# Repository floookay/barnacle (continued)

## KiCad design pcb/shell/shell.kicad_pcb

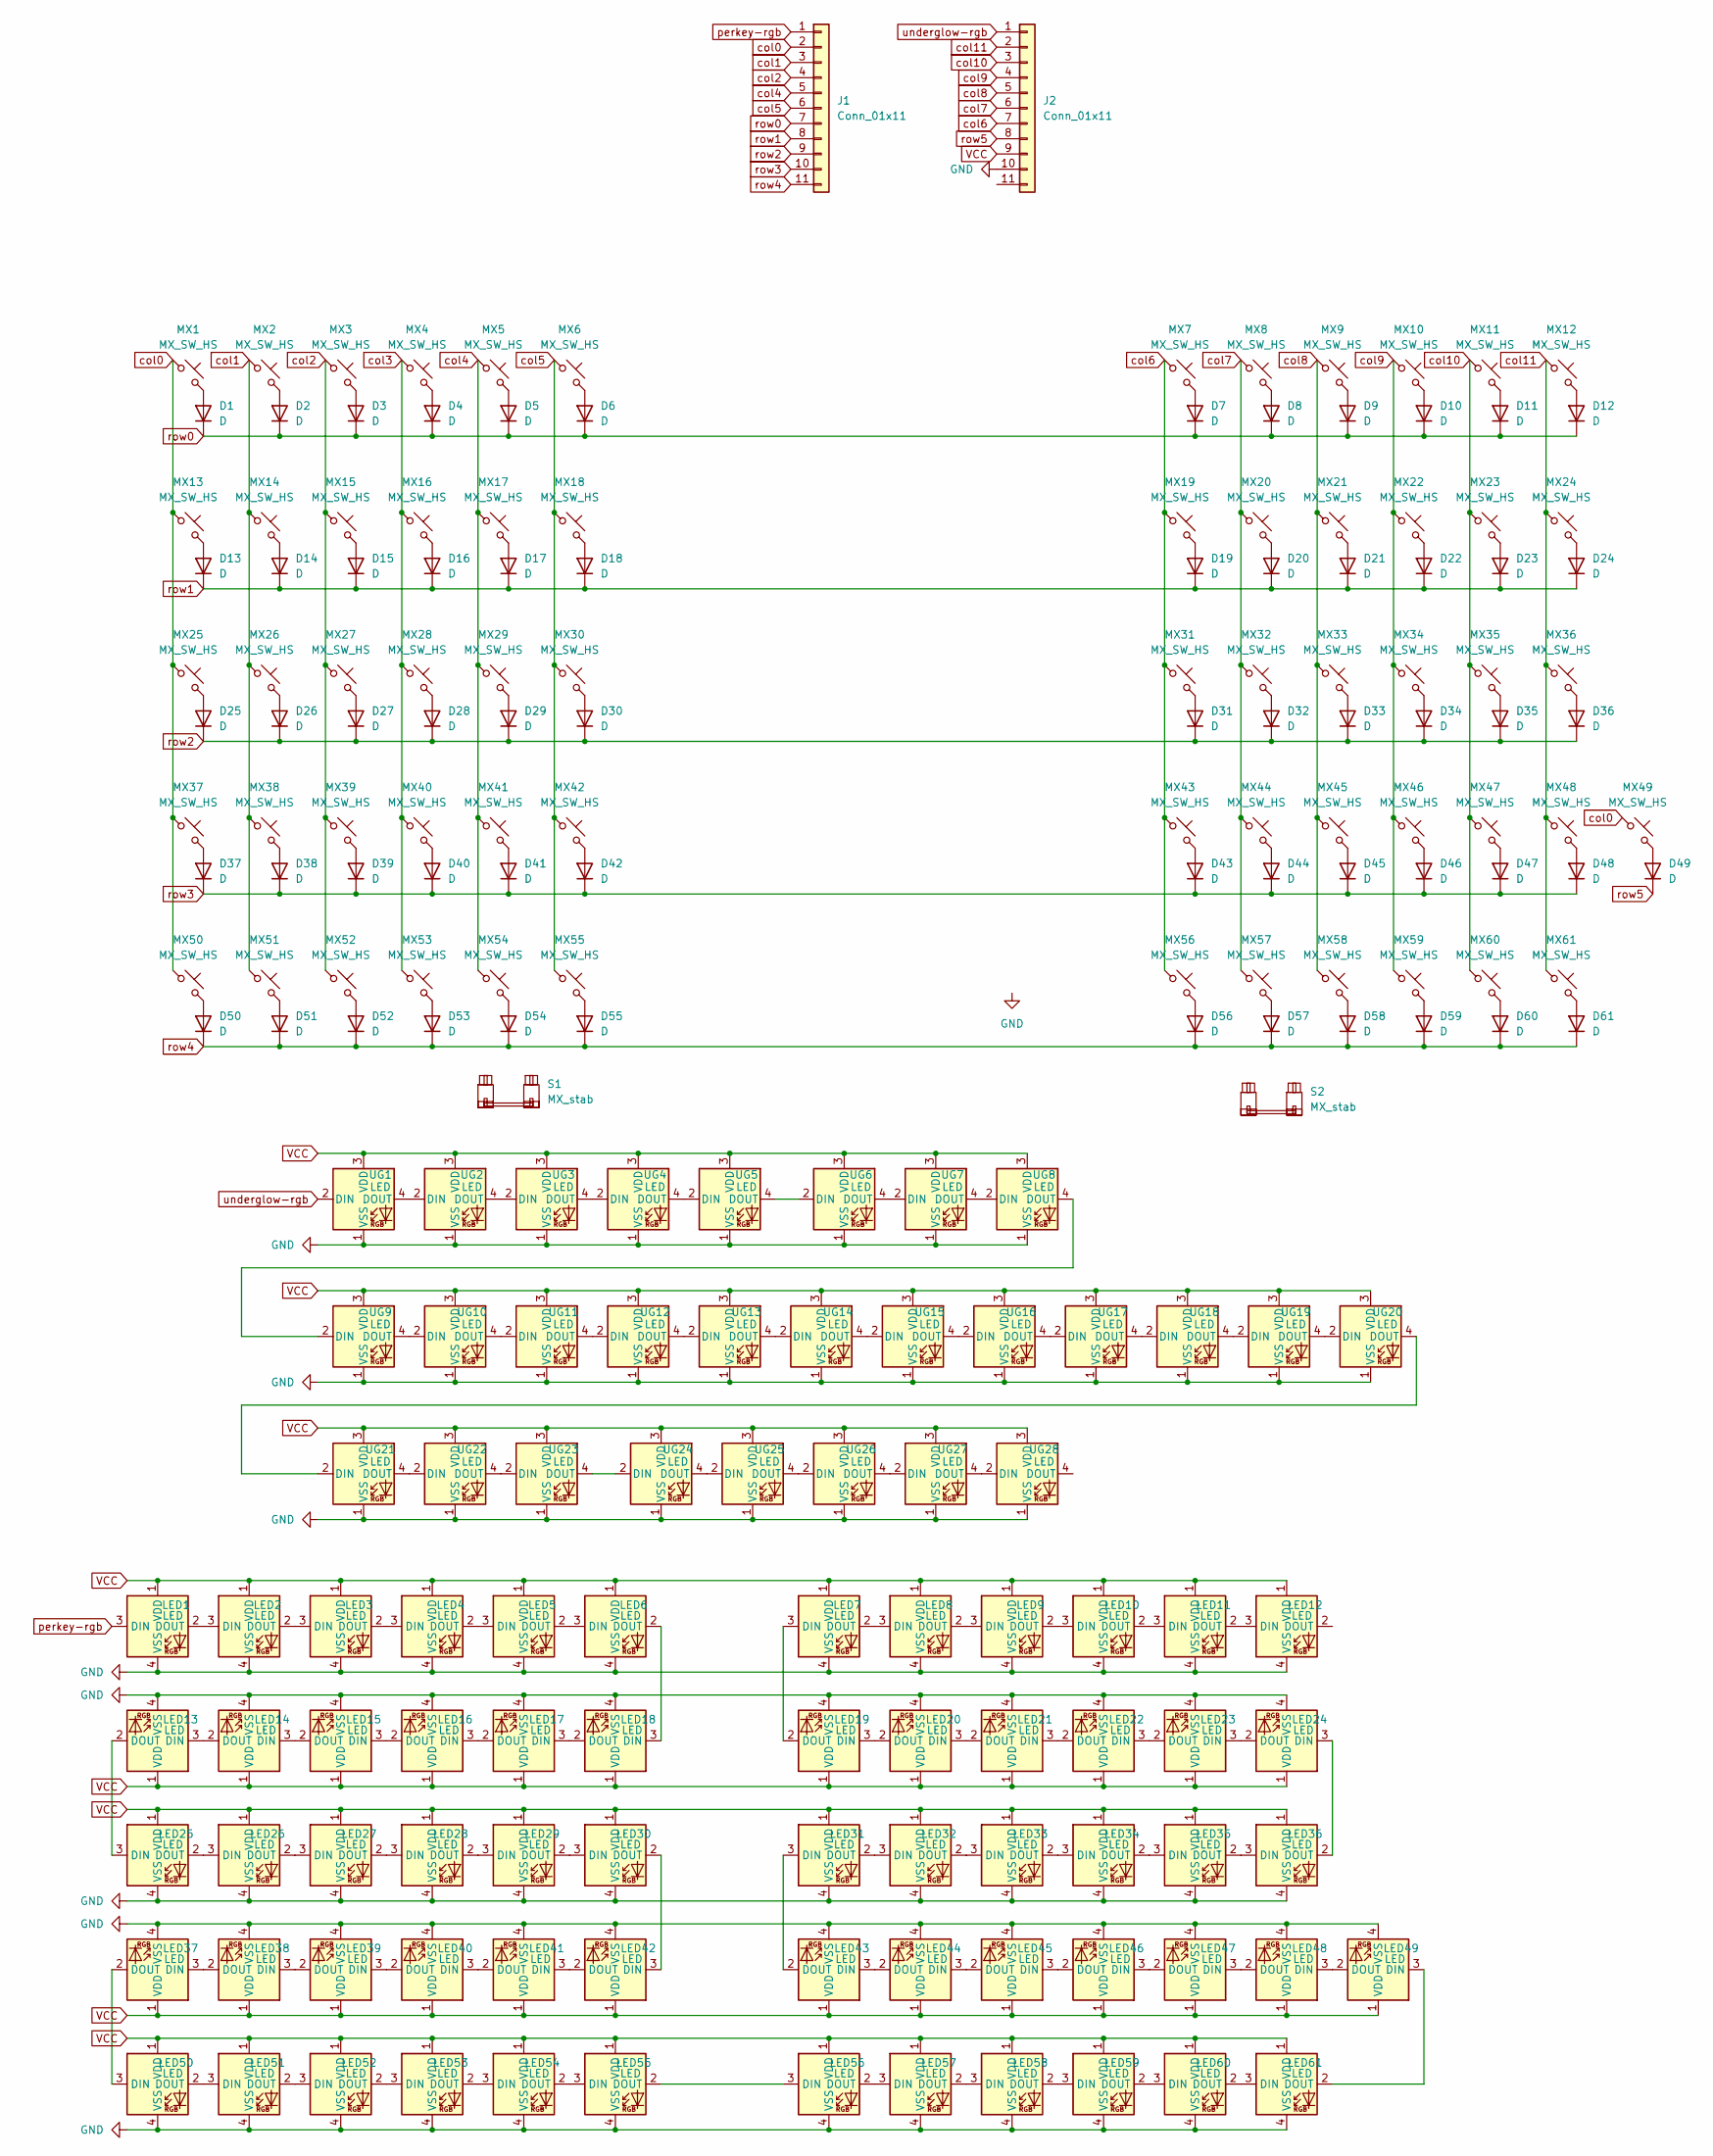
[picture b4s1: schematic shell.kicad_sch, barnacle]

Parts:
D1, D2, D3, D4, D5, D6, D7, D8, D9, D10, D11, D12, D13, D14, D15, D16, D17, D18, D19, D20, D21, D22, D23, D24, D25, D26, D27, D28, D29, D30, D31, D32, D33, D34, D35, D36, D37, D38, D39, D40, D41, D42, D43, D44, D45, D46, D47, D48, D49, D50, D51, D52, D53, D54, D55, D56, D57, D58, D59, D60, D61: D; D_SOD-123
J1, J2: Conn_01x11; PinSocket_1x11_P2.54mm_Vertical
LED1, LED2, LED3, LED4, LED5, LED6, LED7, LED8, LED9, LED10, LED11, LED12, LED25, LED26, LED27, LED28, LED29, LED30, LED31, LED32, LED33, LED34, LED35, LED36, LED50, LED51, LED52, LED53, LED54, LED55, LED56, LED57, LED58, LED59, LED60, LED61: LED; LED_MX_6028R-ROT
LED13, LED14, LED15, LED16, LED17, LED18, LED19, LED20, LED21, LED22, LED23, LED24, LED37, LED38, LED39, LED40, LED41, LED42, LED43, LED44, LED45, LED46, LED47, LED48, LED49: LED; LED_MX_6028R
MX1, MX2, MX3, MX4, MX5, MX6, MX7, MX8, MX9, MX10, MX11, MX12, MX14, MX15, MX16, MX17, MX18, MX19, MX20, MX21, MX22, MX23, MX26, MX27, MX28, MX29, MX30, MX31, MX32, MX33, MX34, MX35, MX38, MX39, MX40, MX41, MX42, MX43, MX44, MX45, MX46, MX47, MX49, MX52, MX54, MX55, MX56, MX57: MX_SW_HS; SW_MX_HS_CPG151101S11_1u
MX13, MX24, MX61: MX_SW_HS; SW_MX_HS_CPG151101S11_1.5u
MX25, MX36, MX37: MX_SW_HS; SW_MX_HS_CPG151101S11_1.75u
MX48, MX50, MX51, MX53, MX58, MX59, MX60: MX_SW_HS; SW_MX_HS_CPG151101S11_1.25u
S1: MX_stab; STAB_MX_P_2.25u
S2: MX_stab; STAB_MX_P_2u
UG1, UG2, UG3, UG4, UG5, UG6, UG7, UG8, UG9, UG10, UG11, UG12, UG13, UG14, UG15, UG16, UG17, UG18, UG19, UG20, UG21, UG22, UG23, UG24, UG25, UG26, UG27, UG28: LED; LED_SK6812_PLCC4_5.0x5.0mm_P3.2mm

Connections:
GND: J2.10, LED1.4 (VSS), LED2.4 (VSS), LED3.4 (VSS), LED4.4 (VSS), LED5.4 (VSS), LED6.4 (VSS), LED7.4 (VSS), LED8.4 (VSS), LED9.4 (VSS), LED10.4 (VSS), LED11.4 (VSS), LED12.4 (VSS), LED13.4 (VSS), LED14.4 (VSS), LED15.4 (VSS), LED16.4 (VSS), LED17.4 (VSS), LED18.4 (VSS), LED19.4 (VSS), LED20.4 (VSS), LED21.4 (VSS), LED22.4 (VSS), LED23.4 (VSS), LED24.4 (VSS), LED25.4 (VSS), LED26.4 (VSS), LED27.4 (VSS), LED28.4 (VSS), LED29.4 (VSS), LED30.4 (VSS), LED31.4 (VSS), LED32.4 (VSS), LED33.4 (VSS), LED34.4 (VSS), LED35.4 (VSS), LED36.4 (VSS), LED37.4 (VSS), LED38.4 (VSS), LED39.4 (VSS), LED40.4 (VSS), LED41.4 (VSS), LED42.4 (VSS), LED43.4 (VSS), LED44.4 (VSS), LED45.4 (VSS), LED46.4 (VSS), LED47.4 (VSS), LED48.4 (VSS), LED49.4 (VSS), LED50.4 (VSS), LED51.4 (VSS), LED52.4 (VSS), LED53.4 (VSS), LED54.4 (VSS), LED55.4 (VSS), LED56.4 (VSS), LED57.4 (VSS), LED58.4 (VSS), LED59.4 (VSS), LED60.4 (VSS), LED61.4 (VSS), UG1.1 (VSS), UG2.1 (VSS), UG3.1 (VSS), UG4.1 (VSS), UG5.1 (VSS), UG6.1 (VSS), UG7.1 (VSS), UG8.1 (VSS), UG9.1 (VSS), UG10.1 (VSS), UG11.1 (VSS), UG12.1 (VSS), UG13.1 (VSS), UG14.1 (VSS), UG15.1 (VSS), UG16.1 (VSS), UG17.1 (VSS), UG18.1 (VSS), UG19.1 (VSS), UG20.1 (VSS), UG21.1 (VSS), UG22.1 (VSS), UG23.1 (VSS), UG24.1 (VSS), UG25.1 (VSS), UG26.1 (VSS), UG27.1 (VSS), UG28.1 (VSS)
unnamed: D1.2 (A), MX1.2
unnamed: D2.2 (A), MX2.2
unnamed: D3.2 (A), MX3.2
unnamed: D4.2 (A), MX4.2
unnamed: D5.2 (A), MX5.2
unnamed: D6.2 (A), MX6.2
unnamed: D7.2 (A), MX7.2
unnamed: D8.2 (A), MX8.2
unnamed: D9.2 (A), MX9.2
unnamed: D10.2 (A), MX10.2
unnamed: D11.2 (A), MX11.2
unnamed: D12.2 (A), MX12.2
unnamed: D13.2 (A), MX13.2
unnamed: D14.2 (A), MX14.2
unnamed: D15.2 (A), MX15.2
unnamed: D16.2 (A), MX16.2
unnamed: D17.2 (A), MX17.2
unnamed: D18.2 (A), MX18.2
unnamed: D19.2 (A), MX19.2
unnamed: D20.2 (A), MX20.2
unnamed: D21.2 (A), MX21.2
unnamed: D22.2 (A), MX22.2
unnamed: D23.2 (A), MX23.2
unnamed: D24.2 (A), MX24.2
unnamed: D25.2 (A), MX25.2
unnamed: D26.2 (A), MX26.2
unnamed: D27.2 (A), MX27.2
unnamed: D28.2 (A), MX28.2
unnamed: D29.2 (A), MX29.2
unnamed: D30.2 (A), MX30.2
unnamed: D31.2 (A), MX31.2
unnamed: D32.2 (A), MX32.2
unnamed: D33.2 (A), MX33.2
unnamed: D34.2 (A), MX34.2
unnamed: D35.2 (A), MX35.2
unnamed: D36.2 (A), MX36.2
unnamed: D37.2 (A), MX37.2
unnamed: D38.2 (A), MX38.2
unnamed: D39.2 (A), MX39.2
unnamed: D40.2 (A), MX40.2
unnamed: D41.2 (A), MX41.2
unnamed: D42.2 (A), MX42.2
unnamed: D43.2 (A), MX43.2
unnamed: D44.2 (A), MX44.2
unnamed: D45.2 (A), MX45.2
unnamed: D46.2 (A), MX46.2
unnamed: D47.2 (A), MX47.2
unnamed: D48.2 (A), MX48.2
unnamed: D49.2 (A), MX49.2
unnamed: D50.2 (A), MX50.2
unnamed: D51.2 (A), MX51.2
unnamed: D52.2 (A), MX52.2
unnamed: D53.2 (A), MX53.2
unnamed: D54.2 (A), MX54.2
unnamed: D55.2 (A), MX55.2
unnamed: D56.2 (A), MX56.2
unnamed: D57.2 (A), MX57.2
unnamed: D58.2 (A), MX58.2
unnamed: D59.2 (A), MX59.2
unnamed: D60.2 (A), MX60.2
unnamed: D61.2 (A), MX61.2
unnamed: LED1.2 (DOUT), LED2.3 (DIN)
unnamed: LED2.2 (DOUT), LED3.3 (DIN)
unnamed: LED3.2 (DOUT), LED4.3 (DIN)
unnamed: LED4.2 (DOUT), LED5.3 (DIN)
unnamed: LED5.2 (DOUT), LED6.3 (DIN)
unnamed: LED7.2 (DOUT), LED8.3 (DIN)
unnamed: LED8.2 (DOUT), LED9.3 (DIN)
unnamed: LED9.2 (DOUT), LED10.3 (DIN)
unnamed: LED10.2 (DOUT), LED11.3 (DIN)
unnamed: LED11.2 (DOUT), LED12.3 (DIN)
unnamed: LED13.3 (DIN), LED14.2 (DOUT)
unnamed: LED13.2 (DOUT), LED25.3 (DIN)
unnamed: LED14.3 (DIN), LED15.2 (DOUT)
unnamed: LED15.3 (DIN), LED16.2 (DOUT)
unnamed: LED16.3 (DIN), LED17.2 (DOUT)
unnamed: LED17.3 (DIN), LED18.2 (DOUT)
unnamed: LED6.2 (DOUT), LED18.3 (DIN)
unnamed: LED19.3 (DIN), LED20.2 (DOUT)
unnamed: LED7.3 (DIN), LED19.2 (DOUT)
unnamed: LED20.3 (DIN), LED21.2 (DOUT)
unnamed: LED21.3 (DIN), LED22.2 (DOUT)
unnamed: LED22.3 (DIN), LED23.2 (DOUT)
unnamed: LED23.3 (DIN), LED24.2 (DOUT)
unnamed: LED24.3 (DIN), LED36.2 (DOUT)
unnamed: LED25.2 (DOUT), LED26.3 (DIN)
unnamed: LED26.2 (DOUT), LED27.3 (DIN)
unnamed: LED27.2 (DOUT), LED28.3 (DIN)
unnamed: LED28.2 (DOUT), LED29.3 (DIN)
unnamed: LED29.2 (DOUT), LED30.3 (DIN)
unnamed: LED30.2 (DOUT), LED42.3 (DIN)
unnamed: LED31.3 (DIN), LED43.2 (DOUT)
unnamed: LED31.2 (DOUT), LED32.3 (DIN)
unnamed: LED32.2 (DOUT), LED33.3 (DIN)
unnamed: LED33.2 (DOUT), LED34.3 (DIN)
unnamed: LED34.2 (DOUT), LED35.3 (DIN)
unnamed: LED35.2 (DOUT), LED36.3 (DIN)
unnamed: LED37.3 (DIN), LED38.2 (DOUT)
unnamed: LED37.2 (DOUT), LED50.3 (DIN)
unnamed: LED38.3 (DIN), LED39.2 (DOUT)
unnamed: LED39.3 (DIN), LED40.2 (DOUT)
unnamed: LED40.3 (DIN), LED41.2 (DOUT)
unnamed: LED41.3 (DIN), LED42.2 (DOUT)
unnamed: LED43.3 (DIN), LED44.2 (DOUT)
unnamed: LED44.3 (DIN), LED45.2 (DOUT)
unnamed: LED45.3 (DIN), LED46.2 (DOUT)
unnamed: LED46.3 (DIN), LED47.2 (DOUT)
unnamed: LED47.3 (DIN), LED48.2 (DOUT)
unnamed: LED48.3 (DIN), LED49.2 (DOUT)
unnamed: LED49.3 (DIN), LED61.2 (DOUT)
unnamed: LED50.2 (DOUT), LED51.3 (DIN)
unnamed: LED51.2 (DOUT), LED52.3 (DIN)
unnamed: LED52.2 (DOUT), LED53.3 (DIN)
unnamed: LED53.2 (DOUT), LED54.3 (DIN)
unnamed: LED54.2 (DOUT), LED55.3 (DIN)
unnamed: LED55.2 (DOUT), LED56.3 (DIN)
unnamed: LED56.2 (DOUT), LED57.3 (DIN)
unnamed: LED57.2 (DOUT), LED58.3 (DIN)
unnamed: LED58.2 (DOUT), LED59.3 (DIN)
unnamed: LED59.2 (DOUT), LED60.3 (DIN)
unnamed: LED60.2 (DOUT), LED61.3 (DIN)
unnamed: UG1.4 (DOUT), UG2.2 (DIN)
unnamed: UG2.4 (DOUT), UG3.2 (DIN)
unnamed: UG3.4 (DOUT), UG4.2 (DIN)
unnamed: UG4.4 (DOUT), UG5.2 (DIN)
unnamed: UG5.4 (DOUT), UG6.2 (DIN)
unnamed: UG6.4 (DOUT), UG7.2 (DIN)
unnamed: UG7.4 (DOUT), UG8.2 (DIN)
unnamed: UG8.4 (DOUT), UG9.2 (DIN)
unnamed: UG9.4 (DOUT), UG10.2 (DIN)
unnamed: UG10.4 (DOUT), UG11.2 (DIN)
unnamed: UG11.4 (DOUT), UG12.2 (DIN)
unnamed: UG12.4 (DOUT), UG13.2 (DIN)
unnamed: UG13.4 (DOUT), UG14.2 (DIN)
unnamed: UG14.4 (DOUT), UG15.2 (DIN)
unnamed: UG15.4 (DOUT), UG16.2 (DIN)
unnamed: UG16.4 (DOUT), UG17.2 (DIN)
unnamed: UG17.4 (DOUT), UG18.2 (DIN)
unnamed: UG18.4 (DOUT), UG19.2 (DIN)
unnamed: UG19.4 (DOUT), UG20.2 (DIN)
unnamed: UG20.4 (DOUT), UG21.2 (DIN)
unnamed: UG21.4 (DOUT), UG22.2 (DIN)
unnamed: UG22.4 (DOUT), UG23.2 (DIN)
unnamed: UG23.4 (DOUT), UG24.2 (DIN)
unnamed: UG24.4 (DOUT), UG25.2 (DIN)
unnamed: UG25.4 (DOUT), UG26.2 (DIN)
unnamed: UG26.4 (DOUT), UG27.2 (DIN)
unnamed: UG27.4 (DOUT), UG28.2 (DIN)
VCC: J2.9, LED1.1 (VDD), LED2.1 (VDD), LED3.1 (VDD), LED4.1 (VDD), LED5.1 (VDD), LED6.1 (VDD), LED7.1 (VDD), LED8.1 (VDD), LED9.1 (VDD), LED10.1 (VDD), LED11.1 (VDD), LED12.1 (VDD), LED13.1 (VDD), LED14.1 (VDD), LED15.1 (VDD), LED16.1 (VDD), LED17.1 (VDD), LED18.1 (VDD), LED19.1 (VDD), LED20.1 (VDD), LED21.1 (VDD), LED22.1 (VDD), LED23.1 (VDD), LED24.1 (VDD), LED25.1 (VDD), LED26.1 (VDD), LED27.1 (VDD), LED28.1 (VDD), LED29.1 (VDD), LED30.1 (VDD), LED31.1 (VDD), LED32.1 (VDD), LED33.1 (VDD), LED34.1 (VDD), LED35.1 (VDD), LED36.1 (VDD), LED37.1 (VDD), LED38.1 (VDD), LED39.1 (VDD), LED40.1 (VDD), LED41.1 (VDD), LED42.1 (VDD), LED43.1 (VDD), LED44.1 (VDD), LED45.1 (VDD), LED46.1 (VDD), LED47.1 (VDD), LED48.1 (VDD), LED49.1 (VDD), LED50.1 (VDD), LED51.1 (VDD), LED52.1 (VDD), LED53.1 (VDD), LED54.1 (VDD), LED55.1 (VDD), LED56.1 (VDD), LED57.1 (VDD), LED58.1 (VDD), LED59.1 (VDD), LED60.1 (VDD), LED61.1 (VDD), UG1.3 (VDD), UG2.3 (VDD), UG3.3 (VDD), UG4.3 (VDD), UG5.3 (VDD), UG6.3 (VDD), UG7.3 (VDD), UG8.3 (VDD), UG9.3 (VDD), UG10.3 (VDD), UG11.3 (VDD), UG12.3 (VDD), UG13.3 (VDD), UG14.3 (VDD), UG15.3 (VDD), UG16.3 (VDD), UG17.3 (VDD), UG18.3 (VDD), UG19.3 (VDD), UG20.3 (VDD), UG21.3 (VDD), UG22.3 (VDD), UG23.3 (VDD), UG24.3 (VDD), UG25.3 (VDD), UG26.3 (VDD), UG27.3 (VDD), UG28.3 (VDD)
col0: J1.2, MX1.1, MX13.1, MX25.1, MX37.1, MX49.1, MX50.1
col1: J1.3, MX2.1, MX14.1, MX26.1, MX38.1, MX51.1
col2: J1.4, MX3.1, MX15.1, MX27.1, MX39.1, MX52.1
col3: MX4.1, MX16.1, MX28.1, MX40.1, MX53.1
col4: J1.5, MX5.1, MX17.1, MX29.1, MX41.1, MX54.1
col5: J1.6, MX6.1, MX18.1, MX30.1, MX42.1, MX55.1
col6: J2.7, MX7.1, MX19.1, MX31.1, MX43.1, MX56.1
col7: J2.6, MX8.1, MX20.1, MX32.1, MX44.1, MX57.1
col8: J2.5, MX9.1, MX21.1, MX33.1, MX45.1, MX58.1
col9: J2.4, MX10.1, MX22.1, MX34.1, MX46.1, MX59.1
col10: J2.3, MX11.1, MX23.1, MX35.1, MX47.1, MX60.1
col11: J2.2, MX12.1, MX24.1, MX36.1, MX48.1, MX61.1
perkey-rgb: J1.1, LED1.3 (DIN)
row0: D1.1 (K), D2.1 (K), D3.1 (K), D4.1 (K), D5.1 (K), D6.1 (K), D7.1 (K), D8.1 (K), D9.1 (K), D10.1 (K), D11.1 (K), D12.1 (K), J1.7
row1: D13.1 (K), D14.1 (K), D15.1 (K), D16.1 (K), D17.1 (K), D18.1 (K), D19.1 (K), D20.1 (K), D21.1 (K), D22.1 (K), D23.1 (K), D24.1 (K), J1.8
row2: D25.1 (K), D26.1 (K), D27.1 (K), D28.1 (K), D29.1 (K), D30.1 (K), D31.1 (K), D32.1 (K), D33.1 (K), D34.1 (K), D35.1 (K), D36.1 (K), J1.9
row3: D37.1 (K), D38.1 (K), D39.1 (K), D40.1 (K), D41.1 (K), D42.1 (K), D43.1 (K), D44.1 (K), D45.1 (K), D46.1 (K), D47.1 (K), D48.1 (K), J1.10
row4: D50.1 (K), D51.1 (K), D52.1 (K), D53.1 (K), D54.1 (K), D55.1 (K), D56.1 (K), D57.1 (K), D58.1 (K), D59.1 (K), D60.1 (K), D61.1 (K), J1.11
row5: D49.1 (K), J2.8
underglow-rgb: J2.1, UG1.2 (DIN)

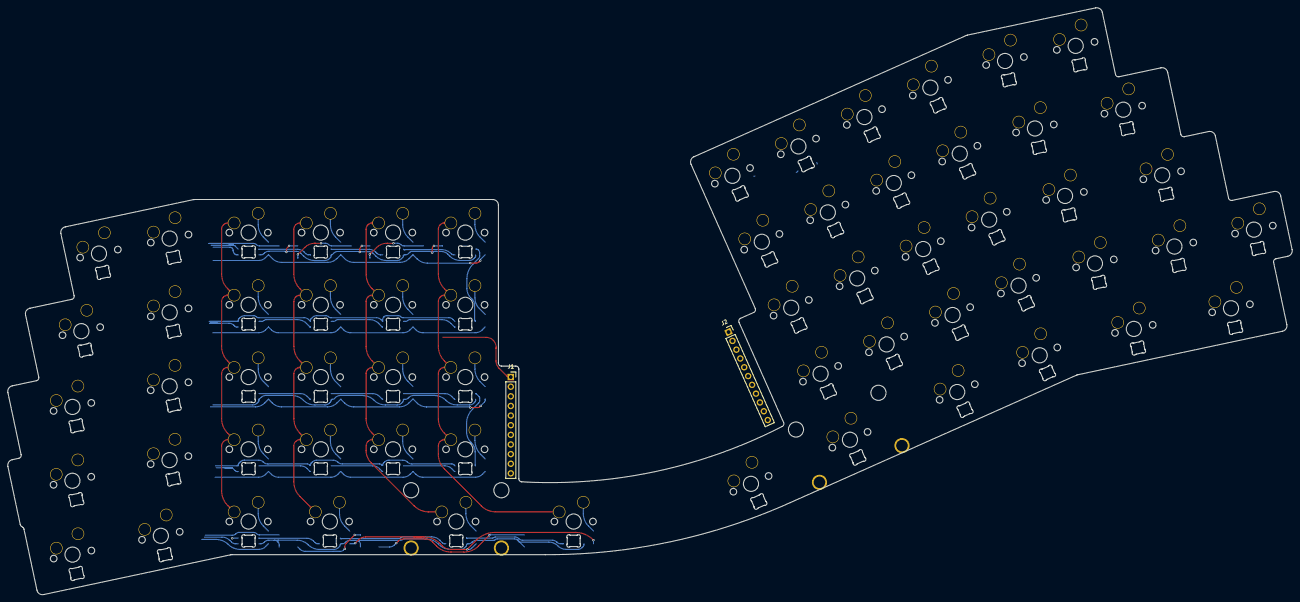
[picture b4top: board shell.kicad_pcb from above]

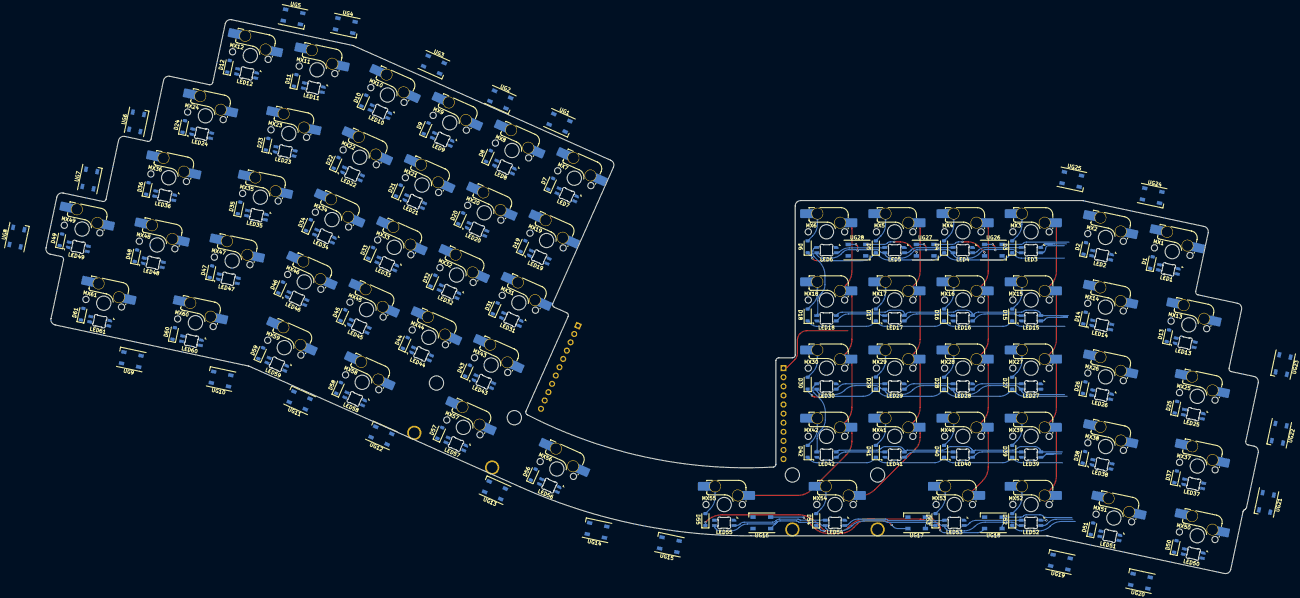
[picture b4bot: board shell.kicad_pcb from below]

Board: 2 copper layers, 338.7 x 154.8 mm, 215 parts (211 on the bottom side), 170 nets.

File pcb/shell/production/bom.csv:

Designator,Footprint,Quantity,Value,LCSC Part #
"D1, D10, D11, D12, D13, D14, D15, D16, D17, D18, D19, D2, D20, D21, D22, D23, D24, D25, D26, D27, D28, D29, D3, D30, D31, D32, D33, D34, D35, D36, D37, D38, D39, D4, D40, D41, D42, D43, D44, D45, D46, D47, D48, D49, D5, D50, D51, D52, D53, D54, D55, D56, D57, D58, D59, D6, D60, D61, D7, D8, D9",D_SOD-123-minimal,61,D,
"J1, J2",PinHeader_1x11_P2.54mm_Vertical,2,Conn_01x11,
"LED1, LED10, LED11, LED12, LED2, LED25, LED26, LED27, LED28, LED29, LED3, LED30, LED31, LED32, LED33, LED34, LED35, LED36, LED4, LED5, LED50, LED51, LED52, LED53, LED54, LED55, LED56, LED57, LED58, LED59, LED6, LED60, LED61, LED7, LED8, LED9",LED_MX_6028R-ROT,36,LED,
"LED13, LED14, LED15, LED16, LED17, LED18, LED19, LED20, LED21, LED22, LED23, LED24, LED37, LED38, LED39, LED40, LED41, LED42, LED43, LED44, LED45, LED46, LED47, LED48, LED49",LED_MX_6028R,25,LED,
"MX1, MX10, MX11, MX12, MX13, MX14, MX15, MX16, MX17, MX18, MX19, MX2, MX20, MX21, MX22, MX23, MX24, MX25, MX26, MX27, MX28, MX29, MX3, MX30, MX31, MX32, MX33, MX34, MX35, MX36, MX37, MX38, MX39, MX4, MX40, MX41, MX42, MX43, MX44, MX45, MX46, MX47, MX48, MX49, MX5, MX50, MX51, MX52, MX53, MX54, MX55, MX56, MX57, MX58, MX59, MX6, MX60, MX61, MX7, MX8, MX9",SW_MX_HS_S_CPG151101S11_1u,61,MX_SW_HS,
S1,STAB_MX_P_2.25u,1,MX_stab,
S2,STAB_MX_P_2u,1,MX_stab,
"UG1, UG10, UG11, UG12, UG13, UG14, UG15, UG16, UG17, UG18, UG19, UG2, UG20, UG21, UG22, UG23, UG24, UG25, UG26, UG27, UG28, UG3, UG4, UG5, UG6, UG7, UG8, UG9",LED_SK6812-combi,28,LED,

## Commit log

2024-06-17 added gitignore
2024-06-17 added prototyping files
2024-06-17 added initial shell pcb files
2024-06-17 added initial case design
2024-06-17 removed bad idea
2024-06-24 backup from yesterday
2024-06-24 backup updated bottom
2024-06-25 finished plate and plate mounting
2024-06-28 adjusted profile angle
2024-06-28 added plate fixers
2024-07-28 updated pcb edge cut
2024-07-28 added core pcb and case chamfers+fillets
2024-08-11 added core case piece
2024-08-11 added bottom plate (again)
2024-08-11 updated screw holes
2024-08-11 added 3x3 core
2024-08-13 wrote a little bit of readme
2024-08-13 fixed per key rgb
2024-08-13 added underglow rgb
2024-08-13 started routing left side
2024-08-14 added a couple more traces on left side
2024-08-14 last commit before rework without rounded tracks
    because of a 100% crash rate when trying to generate the rounded tracks
2024-08-14 finished routing
2024-08-15 added some graphics
2024-08-16 added mounting holes
2024-08-16 added core pcb template
2024-08-17 added two additional encoders
2024-08-17 swap to hardware license
2024-08-17 finished pcbs
2024-08-17 added 3x1 encoder core
2024-08-26 fixed bottom plate
2024-08-30 added 1mm leeway between core case and pcb
2024-08-31 added clamp for top plate fixer
2024-08-31 updated files for 3d printing
2024-08-31 did a little bit of readme
2024-09-01 added knob indentation
2024-09-08 switched rgb back to a regular pin and 3v
2024-09-08 added alignment pins
2024-09-08 added 2.25u core with 2 encoders
2024-09-09 fixed 2.25 grid spacing
2024-09-13 added jumpers for 3.3/5v rgb
2024-10-08 added 3x2 core case
2024-10-08 added folder for user graphics to gitignore
2024-10-08 hid reference designators, simplified footprint silkscreens, added license, added rocks and stones
2024-10-08 added gallery
2024-10-08 restructuring and splitting basic core freecad file
2024-10-12 moved rgb jumpers to the other side
2024-10-12 make library portable
2024-10-12 finished extra core pcb
2024-10-12 renamed core pcbs
2024-10-12 added encoder core
2024-10-12 added versions
2024-10-13 added numblock core pcb
2024-10-13 added cute core pcb (2x2)
2024-10-13 cleaned up readme
2024-10-13 added wooden window case (wip)
2024-10-13 generated fabrication files
2024-10-13 changed sk6812 footprints to be also compatible with sk6812 mini (v1.2)
2024-10-13 add script to correct rotation and added LCSC part numbers
2024-10-27 added tpu plate „foam“
2024-10-27 added missing gnd vias
2024-11-28 added svg with keys
2024-11-28 updated layout
2024-11-28 added script for uploading images
2024-11-28 updated pcb readme
2024-11-29 updated pcb to only use sk6812 mini-e
2024-11-29 wrote a build guide
2024-12-07 updated lcsc number
2024-12-15 updated oled core to fit m2 screws
2024-12-20 fixed rotation of top row underglow leds
    sigh…
2024-12-21 added middle piece for the cute core
2024-12-25 added cross core
2024-12-25 updated build guide and added pictures
2024-12-25 added a comment on the plate file
2024-12-25 updated picture
2024-12-25 added a blank core case piece
2024-12-25 updated case readme
2024-12-28 moved ideas to separate file
2024-12-28 updated readme and added pictures
2024-12-28 removed old note
2024-12-28 fixed link to qmk branch with the firmware
2025-01-04 added a note about the switch above the controller
2025-02-08 added center knob core case
2025-06-25 added printable „weight“
    has to be taped to the acryl
2025-06-25 added vial firmware
2025-06-26 added a small cutout for the usb connector
2025-07-26 added 3x3+1 core
2025-07-26 updated vial firmware
2025-08-09 fixed vial firmware
2025-08-09 updated vial json
2025-08-13 added break off key to the numpad core
2025-08-13 updated readme for numpad core with snap off key
2025-08-13 fixed directory name
2025-08-13 fixed name on pcb
